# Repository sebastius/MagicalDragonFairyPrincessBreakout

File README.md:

# MagicalDragonFairyPrincessBreakout

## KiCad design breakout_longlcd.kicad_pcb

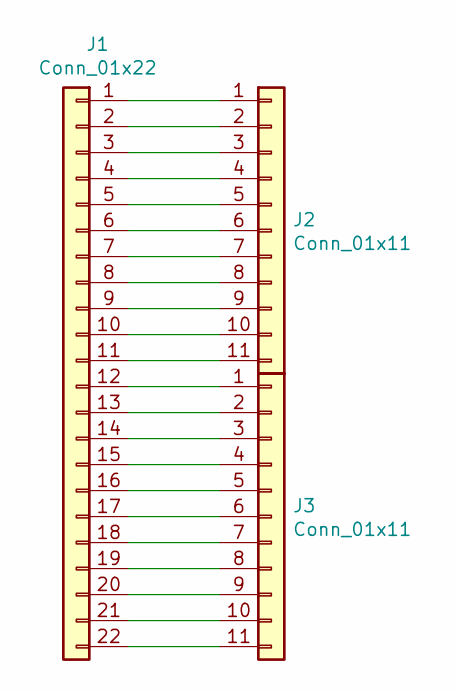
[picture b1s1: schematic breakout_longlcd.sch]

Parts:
J1: Conn_01x22; Hirose_FH12-22S-0.5SH_1x22-1MP_P0.50mm_Horizontal
J2, J3: Conn_01x11; PinHeader_1x11_P2.54mm_Vertical

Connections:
GND: J1.MP
unnamed: J1.1, J2.1
unnamed: J1.2, J2.2
unnamed: J1.3, J2.3
unnamed: J1.4, J2.4
unnamed: J1.5, J2.5
unnamed: J1.6, J2.6
unnamed: J1.7, J2.7
unnamed: J1.8, J2.8
unnamed: J1.9, J2.9
unnamed: J1.10, J2.10
unnamed: J1.11, J2.11
unnamed: J1.12, J3.1
unnamed: J1.13, J3.2
unnamed: J1.14, J3.3
unnamed: J1.15, J3.4
unnamed: J1.16, J3.5
unnamed: J1.17, J3.6
unnamed: J1.18, J3.7
unnamed: J1.19, J3.8
unnamed: J1.20, J3.9
unnamed: J1.21, J3.10
unnamed: J1.22, J3.11

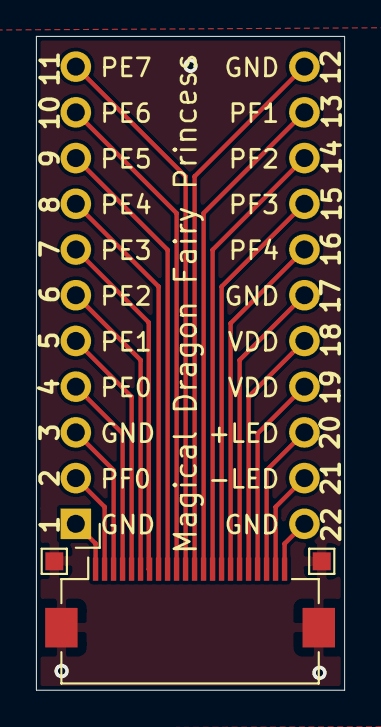
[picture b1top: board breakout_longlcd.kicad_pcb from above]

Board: 2 copper layers, 17.1 x 36.3 mm, 3 parts (0 on the bottom side), 22 nets.

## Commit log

2021-02-13 first commit
    and probably the last.
